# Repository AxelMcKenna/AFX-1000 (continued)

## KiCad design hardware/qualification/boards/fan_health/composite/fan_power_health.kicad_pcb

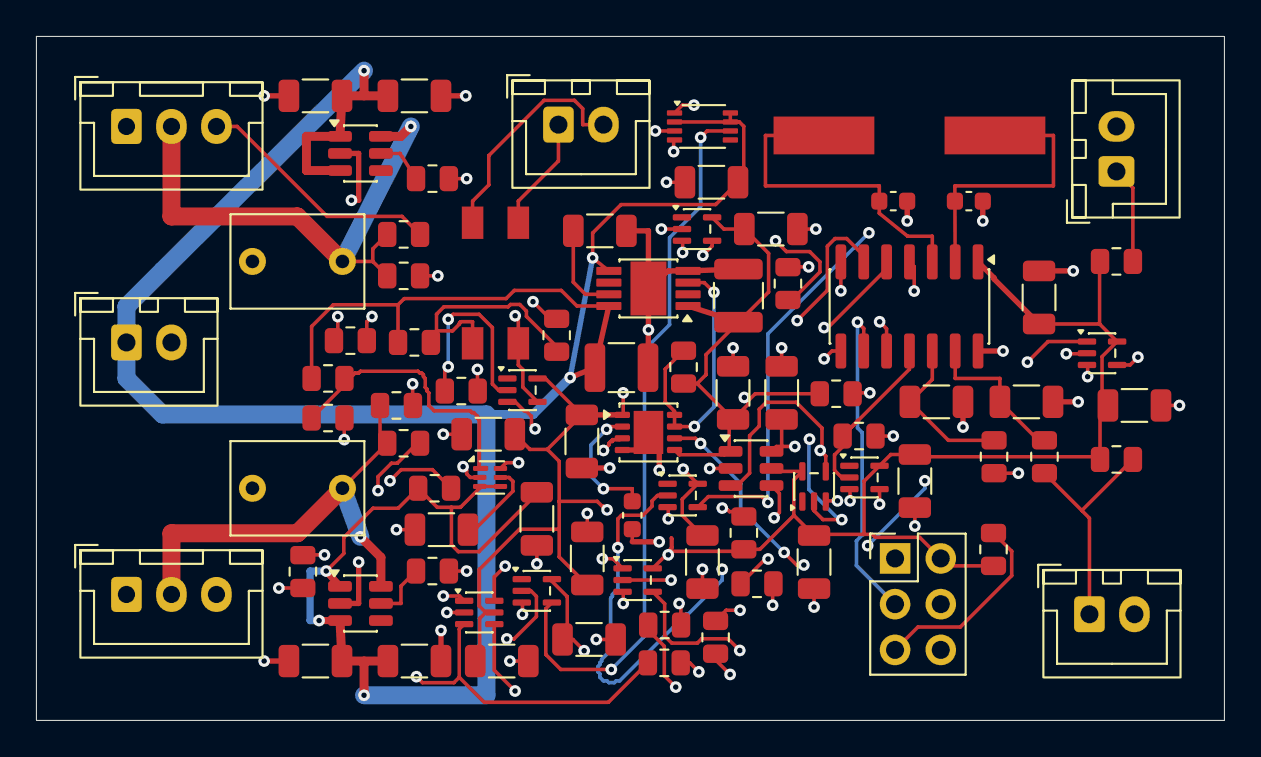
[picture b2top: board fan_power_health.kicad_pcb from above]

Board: 4 copper layers, 66.0 x 38.0 mm, 84 parts (0 on the bottom side), 45 nets.

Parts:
C1, C2: 10uF 25V C3225X7R1E106K250AC; Capacitor_SMD__C_1210_3225Metric
C3, C14, C22, C23: 10nF 50V C0G C1206C103J5GACTU; Capacitor_SMD__C_1206_3216Metric
C4, C5, C6, C8, C9, C10, C11, C12, C13, C15, C16, C17, C18, C19, C24: 100nF 25V C0G C1206C104J3GACTU; Capacitor_SMD__C_1206_3216Metric
C7: 2.7nF 50V C0G5% C0603C272J5GACTU; Capacitor_SMD__C_0603_1608Metric
C20, C21: 15pF 50V C0G5% C0603C150J5GACTU; Capacitor_SMD__C_0603_1608Metric
C201, C202, C301, C302: 100nF25V C0G5% C1206C104J3GACTU; Capacitor_SMD__C_1206_3216Metric
C203, C303: 1uF63V10% WIMA MKS2C041001F00KSSD; Capacitor_THT__C_Rect_L7.2mm_W5.0mm_P5.00mm
J2, J3, J4, J201: JST B2B-XH-A / XHP-2 / SXH-001T-P0.6; Connector_JST__JST_XH_B2B-XH-A_1x02_P2.50mm_Vertical
J5: AVRISP2x3 target-powered3.3V sense ONLY; Connector_PinHeader_2.54mm__PinHeader_2x03_P2.54mm_Vertical
J202, J203: JST B3B-XH-A / XHP-3 / SXH-001T-P0.6; Connector_JST__JST_XH_B3B-XH-A_1x03_P2.50mm_Vertical
R1, R16, R17, R21, R23: 1k 0.1%25ppm TNPW08051K00BEEA; Resistor_SMD__R_0805_2012Metric
R2, R6, R10, R13, R202, R302: 10k 0.1%25ppm TNPW080510K0BEEA; Resistor_SMD__R_0805_2012Metric
R3, R4, R5, R7, R14, R15: 47k 0.1%25ppm TNPW080547K0BEEA; Resistor_SMD__R_0805_2012Metric
R8: 68k 0.1%25ppm TNPW080568K0BEEA; Resistor_SMD__R_0805_2012Metric
R9: 39k 0.1%25ppm TNPW080539K0BEEA; Resistor_SMD__R_0805_2012Metric
R11: 56.2k 0.1%25ppm TNPW080556K2BEEA; Resistor_SMD__R_0805_2012Metric
R12, R24, R201, R203, R301, R303: 100k 0.1%25ppm TNPW0805100KBEEA; Resistor_SMD__R_0805_2012Metric
R20, R22: 20k 0.1%25ppm TNPW080520K0BEEA; Resistor_SMD__R_0805_2012Metric
U1: ATtiny84A-SSUR; Package_SO__SOIC-14_3.9x8.7mm_P1.27mm
U2: TPS7A1633DGNR; TI_DGN0008C
U3: SN74LVC2G17DCKR; Package_TO_SOT_SMD__SOT-363_SC-70-6
U4: TPS3431SDRBR; Package_SON__VSON-8-1EP_3x3mm_P0.65mm_EP1.65x2.4mm
U5: SN74AUP1G17DCKR; Package_TO_SOT_SMD__SOT-353_SC-70-5
U6: SN74LVC1T45DBVR; Package_TO_SOT_SMD__SOT-23-6
U7: SN74LVC1G14DCKR; Package_TO_SOT_SMD__SOT-353_SC-70-5
U8: SN74LVC1G74DCUR; TI_DCU0008A
U9: TPS389001DSET; Package_SON__WSON-6_1.5x1.5mm_P0.5mm
U10, U11: SN74LVC1G17DCKR; Package_TO_SOT_SMD__SOT-353_SC-70-5
U12, U13: SN74LVC1G08DCKR; Package_TO_SOT_SMD__SOT-353_SC-70-5
U14: SN74LVC1G06DCKR; Package_TO_SOT_SMD__SOT-353_SC-70-5
U15: TLP175A(TPL,E); RMX_FH02__TLP175A_11-4M1S_Receiving
U16: SN74LVC1G34DCKR; Package_TO_SOT_SMD__SOT-353_SC-70-5
U201, U301: TPS2553DBVR-1; Package_TO_SOT_SMD__SOT-23-6
X1: ABLS-4.000MHZ-12-D4Y-T; RMX_FH02__ABLS_Manufacturer_Land

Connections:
/E28_POWER_RUN: J4.2, U15.6
/FAN5V_IN: C1.1, C10.1, C11.1, C12.1, C13.1, C15.1, C201.1, C202.1, C301.1, C302.1, J201.1, R1.1, R10.1, R11.1, U2.5, U2.8, U6.6, U7.5, U8.2, U8.7, U8.8, U9.3, U9.4, U10.5, U201.1, U201.3, U301.1, U301.3
/FAN_L_5V: C203.1, J202.2, R202.1, R203.1, U201.6
/FAN_L_ILIM: R201.1, U201.5
/FAN_L_TACH: J202.3, R14.1, R202.2, U3.1
/FAN_R_5V: C303.1, J203.2, R302.1, R303.1, U301.6
/FAN_R_ILIM: R301.1, U301.5
/FAN_R_TACH: J203.3, R15.1, R302.2, U3.3
/FAULT_CLK: U7.4, U8.1
/GND: C1.2, C2.2, C3.2, C4.2, C5.2, C6.2, C7.2, C8.2, C9.2, C10.2, C11.2, C12.2, C13.2, C14.2, C15.2, C16.2, C17.2, C18.2, C19.2, C20.2, C21.2, C22.2, C23.2, C24.2, C201.2, C202.2, C203.2, C301.2, C302.2, C303.2, J2.2, J3.2, J5.6, J201.2, J202.1, J203.1, R3.2, R4.2, R8.2, R9.2, R12.2, R13.2, R14.2, R15.2, R24.2, R201.2, R203.2, R301.2, R303.2, U1.14, U2.4, U2.9, U3.2, U4.4, U4.9, U5.3, U6.2, U7.3, U8.4, U9.2, U10.3, U11.3, U12.3, U13.3, U14.3, U16.3, U201.2, U301.2
/HEALTH_AND_WD: U12.4, U13.1
/HEARTBEAT: R4.1, U1.11, U16.2
/HEARTBEAT_FAST: U4.6, U16.4
/HW_NOFAULT: U11.4, U13.2
/HW_NOFAULT_5: R9.1, U8.3, U11.2
/ISP_MISO: J5.1, U1.8
/ISP_MOSI: J5.4, U1.7
/ISP_SCK: J5.3, U1.9
/LDO_DELAY: C3.1, U2.7
/LEAF_PERMISSION: R13.1, U13.4, U14.2
/LED_A: R1.2, R2.1, U15.1
/LED_K: R2.2, U14.4, U15.3
/MCU_HEALTH: R3.1, U1.6, U12.1
/MCU_RESET_N: J5.5, R6.2, U1.4
/MCU_TACH_L: R16.2, U1.10
/MCU_TACH_R: R17.2, U1.5
/P03_POWER_RUN: J4.1, U15.4
/RAW_CLEAR_FAST: U8.6, U10.4
/RAW_CLEAR_N: R10.2, U9.6, U10.2
/RAW_POR_CT: C14.1, U9.5
/RAW_POR_SENSE: R11.2, R12.1, U9.1
/TACH_L_BUF: R16.1, U3.6
/TACH_R_BUF: R17.1, U3.4
/TEMP_L_ADC: C22.1, R21.2, U1.13
/TEMP_L_NODE: J2.1, R20.2, R21.1
/TEMP_R_ADC: C23.1, R23.2, U1.12
/TEMP_R_NODE: J3.1, R22.2, R23.1
/V3V3: C2.1, C4.1, C5.1, C6.1, C8.1, C9.1, C16.1, C17.1, C18.1, C19.1, C24.1, J5.2, R5.1, R6.1, R7.1, R20.1, R22.1, R24.1, U1.1, U2.1, U3.5, U4.1, U4.5, U5.5, U6.1, U6.5, U11.5, U12.5, U13.5, U14.5, U16.5
/WD_CWD: C7.1, U4.2
/WD_EN: R7.2, U4.3
/WD_OK: R5.2, U2.3, U4.7, U4.8, U5.2
/WD_OK_5: R8.1, U6.4, U7.2
/WD_OK_FAST: U5.4, U6.3, U12.2
/XTAL1: C20.1, U1.2, X1.1
/XTAL2: C21.1, U1.3, X1.2

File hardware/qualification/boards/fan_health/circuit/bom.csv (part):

Reference,Part_or_value,Footprint,Source,Note
U1,ATtiny84A-SSUR,Package_SO:SOIC-14_3.9x8.7mm_P1.27mm,https://ww1.microchip.com/downloads/en/DeviceDoc/ATtiny24A-4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,"Microchip DS40002269A source bytes captured. External4MHz crystal; CPU4MHz, Timer1/8, ADC/64 per captured root firmware. 3mA VCC-pin current is receiving, NOT a transferable bare-external-clock table guarantee."
U2,TPS7A1633DGNR,Package_SO:HVSSOP-8-1EP_3x3mm_P0.65mm_EP1.57x1.89mm,https://www.ti.com/lit/ds/symlink/tps7a16.pdf,"Fixed output: pin2 MUST remain unconnected. PG joins open-drain WD_OK; rising85..95% output threshold is not a precision3.3V monitor. All regulator caps same FRONT face, local direct ground in future layout."
U3,SN74LVC2G17DCKR,Package_TO_SOT_SMD:SOT-363_SC-70-6,https://www.ti.com/lit/ds/symlink/sn74lvc2g17.pdf,5.5V tolerant Schmitt inputs/Ioff. Fan-side pullups follow switched5V in FP01; no always-on pullup phantom-feed.
U4,TPS3431SDRBR,Package_SON:VSON-8-1EP_3x3mm_P0.65mm_EP1.65x2.4mm,https://www.ti.com/lit/ds/symlink/tps3431.pdf,"TI permits tying ENOUT/WDO. Timeout independently blocks permission and clocksRAW5latch; it doesNOTdriveMCURESET, because startupENOUTLOW would createEXTRF and conflictwithcleanPOR firmware. Watchdogretry MUST NOT reclosecontact."
U5,SN74AUP1G17DCKR,Package_TO_SOT_SMD:SOT-353_SC-70-5,https://www.ti.com/lit/ds/symlink/sn74aup1g17.pdf,
U6,SN74LVC1T45DBVR,Package_TO_SOT_SMD:SOT-23-6,https://www.ti.com/lit/ds/symlink/sn74lvc1t45.pdf,A-to-B; either supply atGND isolates both ports. RAW5 B pulldown forces fault on complete3.3V loss; intermediate-rail behavior remains receiving.
U7,SN74LVC1G14DCKR,Package_TO_SOT_SMD:SOT-353_SC-70-5,https://www.ti.com/lit/ds/symlink/sn74lvc1g14.pdf,
U8,SN74LVC1G74DCUR,Package_SO:VSSOP-8_2.3x2mm_P0.5mm,https://www.ti.com/lit/ds/symlink/sn74lvc1g74.pdf,IndependentRAW5-powered positive-edge latch; D=1. First watchdog failure storesQ=1/Q_N=0 until RAW5 power-cycle clear. 3.3V-only resets cannot intentionally clear it.
U9,TPS389001DSET,Package_SON:WSON-6_1.5x1.5mm_P0.5mm,https://www.ti.com/lit/ds/symlink/tps3890.pdf,"Dedicatedrawpower-cycle clear nominal1.7963V; assertion/deassertion and1.65V latch retention crossover must be characterized. CT delays clear RELEASE, not fault capture."
U10,SN74LVC1G17DCKR,Package_TO_SOT_SMD:SOT-353_SC-70-5,https://www.ti.com/lit/ds/symlink/sn74lvc1g17.pdf,
U11,SN74LVC1G17DCKR,Package_TO_SOT_SMD:SOT-353_SC-70-5,https://www.ti.com/lit/ds/symlink/sn74lvc1g17.pdf,
U12,SN74LVC1G08DCKR,Package_TO_SOT_SMD:SOT-353_SC-70-5,https://www.ti.com/lit/ds/symlink/sn74lvc1g08.pdf,2.0V VIH applies over actual3.0..3.6V supply row. All inputs have active push-pull drivers; rawopen-drain WD_OK is Schmittconditioned first.
U13,SN74LVC1G08DCKR,Package_TO_SOT_SMD:SOT-353_SC-70-5,https://www.ti.com/lit/ds/symlink/sn74lvc1g08.pdf,2.0V VIH applies over actual3.0..3.6V supply row. All inputs have active push-pull drivers; rawopen-drain WD_OK is Schmittconditioned first.
U14,SN74LVC1G06DCKR,Package_TO_SOT_SMD:SOT-353_SC-70-5,https://www.ti.com/lit/ds/symlink/sn74lvc1g06.pdf,
U16,SN74LVC1G34DCKR,Package_TO_SOT_SMD:SOT-353_SC-70-5,https://www.ti.com/lit/ds/symlink/sn74lvc1g34.pdf,
U15,"TLP175A(TPL,E)",RMX_FH02:TLP175A_11-4M1S_Receiving,https://toshiba.semicon-storage.com/info/TLP175A_datasheet_e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,Normally-open isolated contact ONLY P03J106.3→E28J5.3. 1/3LED and4/6contact exact pins. Recommendedambient≤65°C. No E28_MASTER_ENABLE connection.
X1,ABLS-4.000MHZ-12-D4Y-T,RMX_FH02:ABLS_Manufacturer_Land,https://abracon.com/Resonators/abls.pdf,4MHzfundamental/CL12pF/−40..85C/initial±30ppm/temp±30ppm. Manufacturerland5.6x2.1mm/9.5mmcentres. 15pF+15pF assumes4.5pFstray; drive/startup/complete±0.1%clock requires receiving tests.
R1,1k 0.1%25ppm TNPW08051K00BEEA,Resistor_SMD:R_0805_2012Metric,https://www.vishay.com/docs/28758/tnpw_e3.pdf,Complete±3%; feed branch includes shunt current once.
R2,10k 0.1%25ppm TNPW080510K0BEEA,Resistor_SMD:R_0805_2012Metric,https://www.vishay.com/docs/28758/tnpw_e3.pdf,"Complete±3%; across LED, not merely gate pulldown. Ioff10uA creates≤.103VLED in settled model."
R3,47k 0.1%25ppm TNPW080547K0BEEA,Resistor_SMD:R_0805_2012Metric,https://www.vishay.com/docs/28758/tnpw_e3.pdf,DefaultOFF duringMCUreset/input state.
R4,47k 0.1%25ppm TNPW080547K0BEEA,Resistor_SMD:R_0805_2012Metric,https://www.vishay.com/docs/28758/tnpw_e3.pdf,No floatingWDI whileMCUreset.
R5,47k 0.1%25ppm TNPW080547K0BEEA,Resistor_SMD:R_0805_2012Metric,https://www.vishay.com/docs/28758/tnpw_e3.pdf,Open-drainwatchdog/PG pullup.
R6,10k 0.1%25ppm TNPW080510K0BEEA,Resistor_SMD:R_0805_2012Metric,https://www.vishay.com/docs/28758/tnpw_e3.pdf,MCURESET externalpullup; internal30..60k table at5.5V is not our full3.3V bound. ExternalwatchdogdoesNOTdriveRESET; avoidsstartupEXTRF.
R7,47k 0.1%25ppm TNPW080547K0BEEA,Resistor_SMD:R_0805_2012Metric,https://www.vishay.com/docs/28758/tnpw_e3.pdf,WDalwaysenabled; manufacturing must not leave bypass fitted.
R8,68k 0.1%25ppm TNPW080568K0BEEA,Resistor_SMD:R_0805_2012Metric,https://www.vishay.com/docs/28758/tnpw_e3.pdf,Complete±3%; 1T45off2uA+G14input5uA gives≤.49028V.
R9,39k 0.1%25ppm TNPW080539K0BEEA,Resistor_SMD:R_0805_2012Metric,https://www.vishay.com/docs/28758/tnpw_e3.pdf,Complete±3%; rawFFIoff10uA+G17input5uA gives≤.60255V.
R10,10k 0.1%25ppm TNPW080510K0BEEA,Resistor_SMD:R_0805_2012Metric,https://www.vishay.com/docs/28758/tnpw_e3.pdf,SupervisorOCpullup; Schmitt before ordinaryCLR input.
R11,56.2k 0.1%25ppm TNPW080556K2BEEA,Resistor_SMD:R_0805_2012Metric,https://www.vishay.com/docs/28758/tnpw_e3.pdf,Complete±1% receiving.
R12,100k 0.1%25ppm TNPW0805100KBEEA,Resistor_SMD:R_0805_2012Metric,https://www.vishay.com/docs/28758/tnpw_e3.pdf,Complete±1% receiving.
R13,10k 0.1%25ppm TNPW080510K0BEEA,Resistor_SMD:R_0805_2012Metric,https://www.vishay.com/docs/28758/tnpw_e3.pdf,LEDsinkdefaultOFF whenlogicoutputs highZ;10uAoutputIoff+5uAinputleak→≤.1545V givencomplete±3%R. Intermediatepowerstillrequirescharacterization.
R14,47k 0.1%25ppm TNPW080547K0BEEA,Resistor_SMD:R_0805_2012Metric,https://www.vishay.com/docs/28758/tnpw_e3.pdf,Receiveropen-wiredefaultLOW; sourcepullup current already inFP01ledger.
R15,47k 0.1%25ppm TNPW080547K0BEEA,Resistor_SMD:R_0805_2012Metric,https://www.vishay.com/docs/28758/tnpw_e3.pdf,Receiveropen-wiredefaultLOW; noextraalways-on5Vpullup.
R16,1k 0.1%25ppm TNPW08051K00BEEA,Resistor_SMD:R_0805_2012Metric,https://www.vishay.com/docs/28758/tnpw_e3.pdf,Edge/ISR error must be measured with this actualRC.
R17,1k 0.1%25ppm TNPW08051K00BEEA,Resistor_SMD:R_0805_2012Metric,https://www.vishay.com/docs/28758/tnpw_e3.pdf,Edge/ISR error must be measured with this actualRC.
R20,20k 0.1%25ppm TNPW080520K0BEEA,Resistor_SMD:R_0805_2012Metric,https://www.vishay.com/docs/28758/tnpw_e3.pdf,Complete±.5% receiving; exact203AT-2current/thermalcoupling unqualified.
R21,1k 0.1%25ppm TNPW08051K00BEEA,Resistor_SMD:R_0805_2012Metric,https://www.vishay.com/docs/28758/tnpw_e3.pdf,Complete±3% receiving; totalADC+capacitorleak±1.1uA receiving.
R22,20k 0.1%25ppm TNPW080520K0BEEA,Resistor_SMD:R_0805_2012Metric,https://www.vishay.com/docs/28758/tnpw_e3.pdf,Complete±.5% receiving.
R23,1k 0.1%25ppm TNPW08051K00BEEA,Resistor_SMD:R_0805_2012Metric,https://www.vishay.com/docs/28758/tnpw_e3.pdf,Complete±3% receiving.
R24,100k 0.1%25ppm TNPW0805100KBEEA,Resistor_SMD:R_0805_2012Metric,https://www.vishay.com/docs/28758/tnpw_e3.pdf,Complete±3% minimum-loadbleed:≥31.4uA at3.234V keepsLDOabove10uAaccuracycondition evenifMCU/sensorsquiet.
C1,10uF 25V C3225X7R1E106K250AC,Capacitor_SMD:C_1210_3225Metric,https://product.tdk.com/en/search/capacitor/ceramic/mlcc/inf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,RequiredlocalFRONTinputcap; effective≥.1uF (project≥3uF receiving) acrossallcorners.
C2,10uF 25V C3225X7R1E106K250AC,Capacitor_SMD:C_1210_3225Metric,https://product.tdk.com/en/search/capacitor/ceramic/mlcc/inf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,RequiredlocalFRONToutputcap; effective≥2.2uF (project≥3uF receiving). ExactESR/stability notproved bynominal10uF.
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
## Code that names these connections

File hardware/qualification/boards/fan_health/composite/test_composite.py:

"""Actual native composition, interface and destructive-mutation regressions."""

import copy
import json
import unittest

from hardware.electronics.common.sexpr import a, children, first, read_sexpr
from hardware.qualification.boards.fan_health.composite.review import (
    ROOT,
    by_ref,
    native_pins,
    sha,
    validate_tree,
)


class CompositeTests(unittest.TestCase):
    @classmethod
    def setUpClass(cls):
        cls.tree = read_sexpr((ROOT / "fan_power_health.kicad_pcb").read_text())

    def test_actual_native_closed_and_source_bound(self):
        report = json.loads((ROOT / "generated/final-review.json").read_text())
        for name, digest in report["sources_sha256"].items():
            self.assertEqual(sha(ROOT / name), digest, name)
        self.assertEqual(validate_tree(self.tree)["parts"], 84)
        for n in ["schematic_ERC_errors", "PCB_hard_DRC", "warnings", "opens", "schematic_parity"]:
            self.assertEqual(report[n], 0)
        self.assertFalse(report["physical_qualified"])
        self.assertFalse(report["fabrication_released"])

    def test_exact_parent_pin_equivalence_except_declared_headers(self):
        parts = json.loads((ROOT / "components.json").read_text())
        for parent in ["FH02", "FP01"]:
            original = {
                c["ref"]: c for c in json.loads((ROOT / "sources" / parent / "components.json").read_text())
            }
            for c in [c for c in parts if c["parent"] == parent]:
                old = original[c["parent_ref"]]
                expected = {
                    p["number"]: (
                        None
                        if parent == "FP01" and p["net"] in ["FAN_L_FAULT_N", "FAN_R_FAULT_N"]
                        else "GND"
                        if parent == "FP01" and p["net"] == "FAN_GND"
                        else p["net"]
                    )
                    for p in old["pins"]
                }
                self.assertEqual({p["number"]: p["net"] for p in c["pins"]}, expected, c["ref"])
        self.assertEqual(len(parts), 68 + 18 - 2)

    def test_raw_fault_latch_independent_of_mcu_reset(self):
        pins = native_pins(self.tree)
        self.assertEqual(pins["U8"]["8"], "FAN5V_IN")
        self.assertEqual(pins["U8"]["1"], "FAULT_CLK")
        self.assertEqual(pins["U8"]["6"], "RAW_CLEAR_FAST")
        self.assertNotEqual(pins["U8"]["6"], pins["U1"]["4"])
        self.assertEqual(pins["U8"]["3"], "HW_NOFAULT_5")

    def test_same_value_smaller_timing_cap_and_retained_poses(self):
        parts = {c["ref"]: c for c in json.loads((ROOT / "components.json").read_text())}
        self.assertIn("2.7nF", parts["C7"]["part"])
        self.assertIn("C0603C272J5GACTU", parts["C7"]["part"])
        review = json.loads((ROOT / "generated/final-review.json").read_text())
        self.assertEqual(review["unchanged_complete_footprints"], 83)
        self.assertTrue(review["all84_poses_preserved"])

    def test_sensor_swap_rejected(self):
        t = copy.deepcopy(self.tree)
        p = next(p for p in children(by_ref(t)["U1"], "pad") if p[1] == "13")
        first(p, "net")[1] = a("/TEMP_R_ADC")
        with self.assertRaises(AssertionError):
            validate_tree(t)

    def test_signal_plane_cut_rejected(self):
        t = copy.deepcopy(self.tree)
        track = copy.deepcopy(children(t, "segment")[0])
        first(track, "layer")[1] = a("In1.Cu")
        t.append(track)
        with self.assertRaisesRegex(AssertionError, "Dedicated return"):
            validate_tree(t)

    def test_removed_pad_via_exclusion_rejected(self):
        t = copy.deepcopy(self.tree)
        zone = next(
            z
            for z in children(t, "zone")
            if children(z, "name") and first(z, "name")[1] == "NO_UNFILLED_VIP_C7_1"
        )
        t.remove(zone)
        with self.assertRaisesRegex(AssertionError, "via exclusion"):
            validate_tree(t)

    def test_clock_route_deletion_rejected(self):
        t = copy.deepcopy(self.tree)
        track = next(s for s in children(t, "segment") if first(s, "net")[1] == "/XTAL1")
        t.remove(track)
        with self.assertRaisesRegex(AssertionError, "Lost literal"):
            validate_tree(t)

    def test_wrong_power_run_leaf_rejected(self):
        t = copy.deepcopy(self.tree)
        p = next(p for p in children(by_ref(t)["J4"], "pad") if p[1] == "2")
        first(p, "net")[1] = a("/E28_MASTER_ENABLE")
        with self.assertRaises(AssertionError):
            validate_tree(t)


if __name__ == "__main__":
    unittest.main()
